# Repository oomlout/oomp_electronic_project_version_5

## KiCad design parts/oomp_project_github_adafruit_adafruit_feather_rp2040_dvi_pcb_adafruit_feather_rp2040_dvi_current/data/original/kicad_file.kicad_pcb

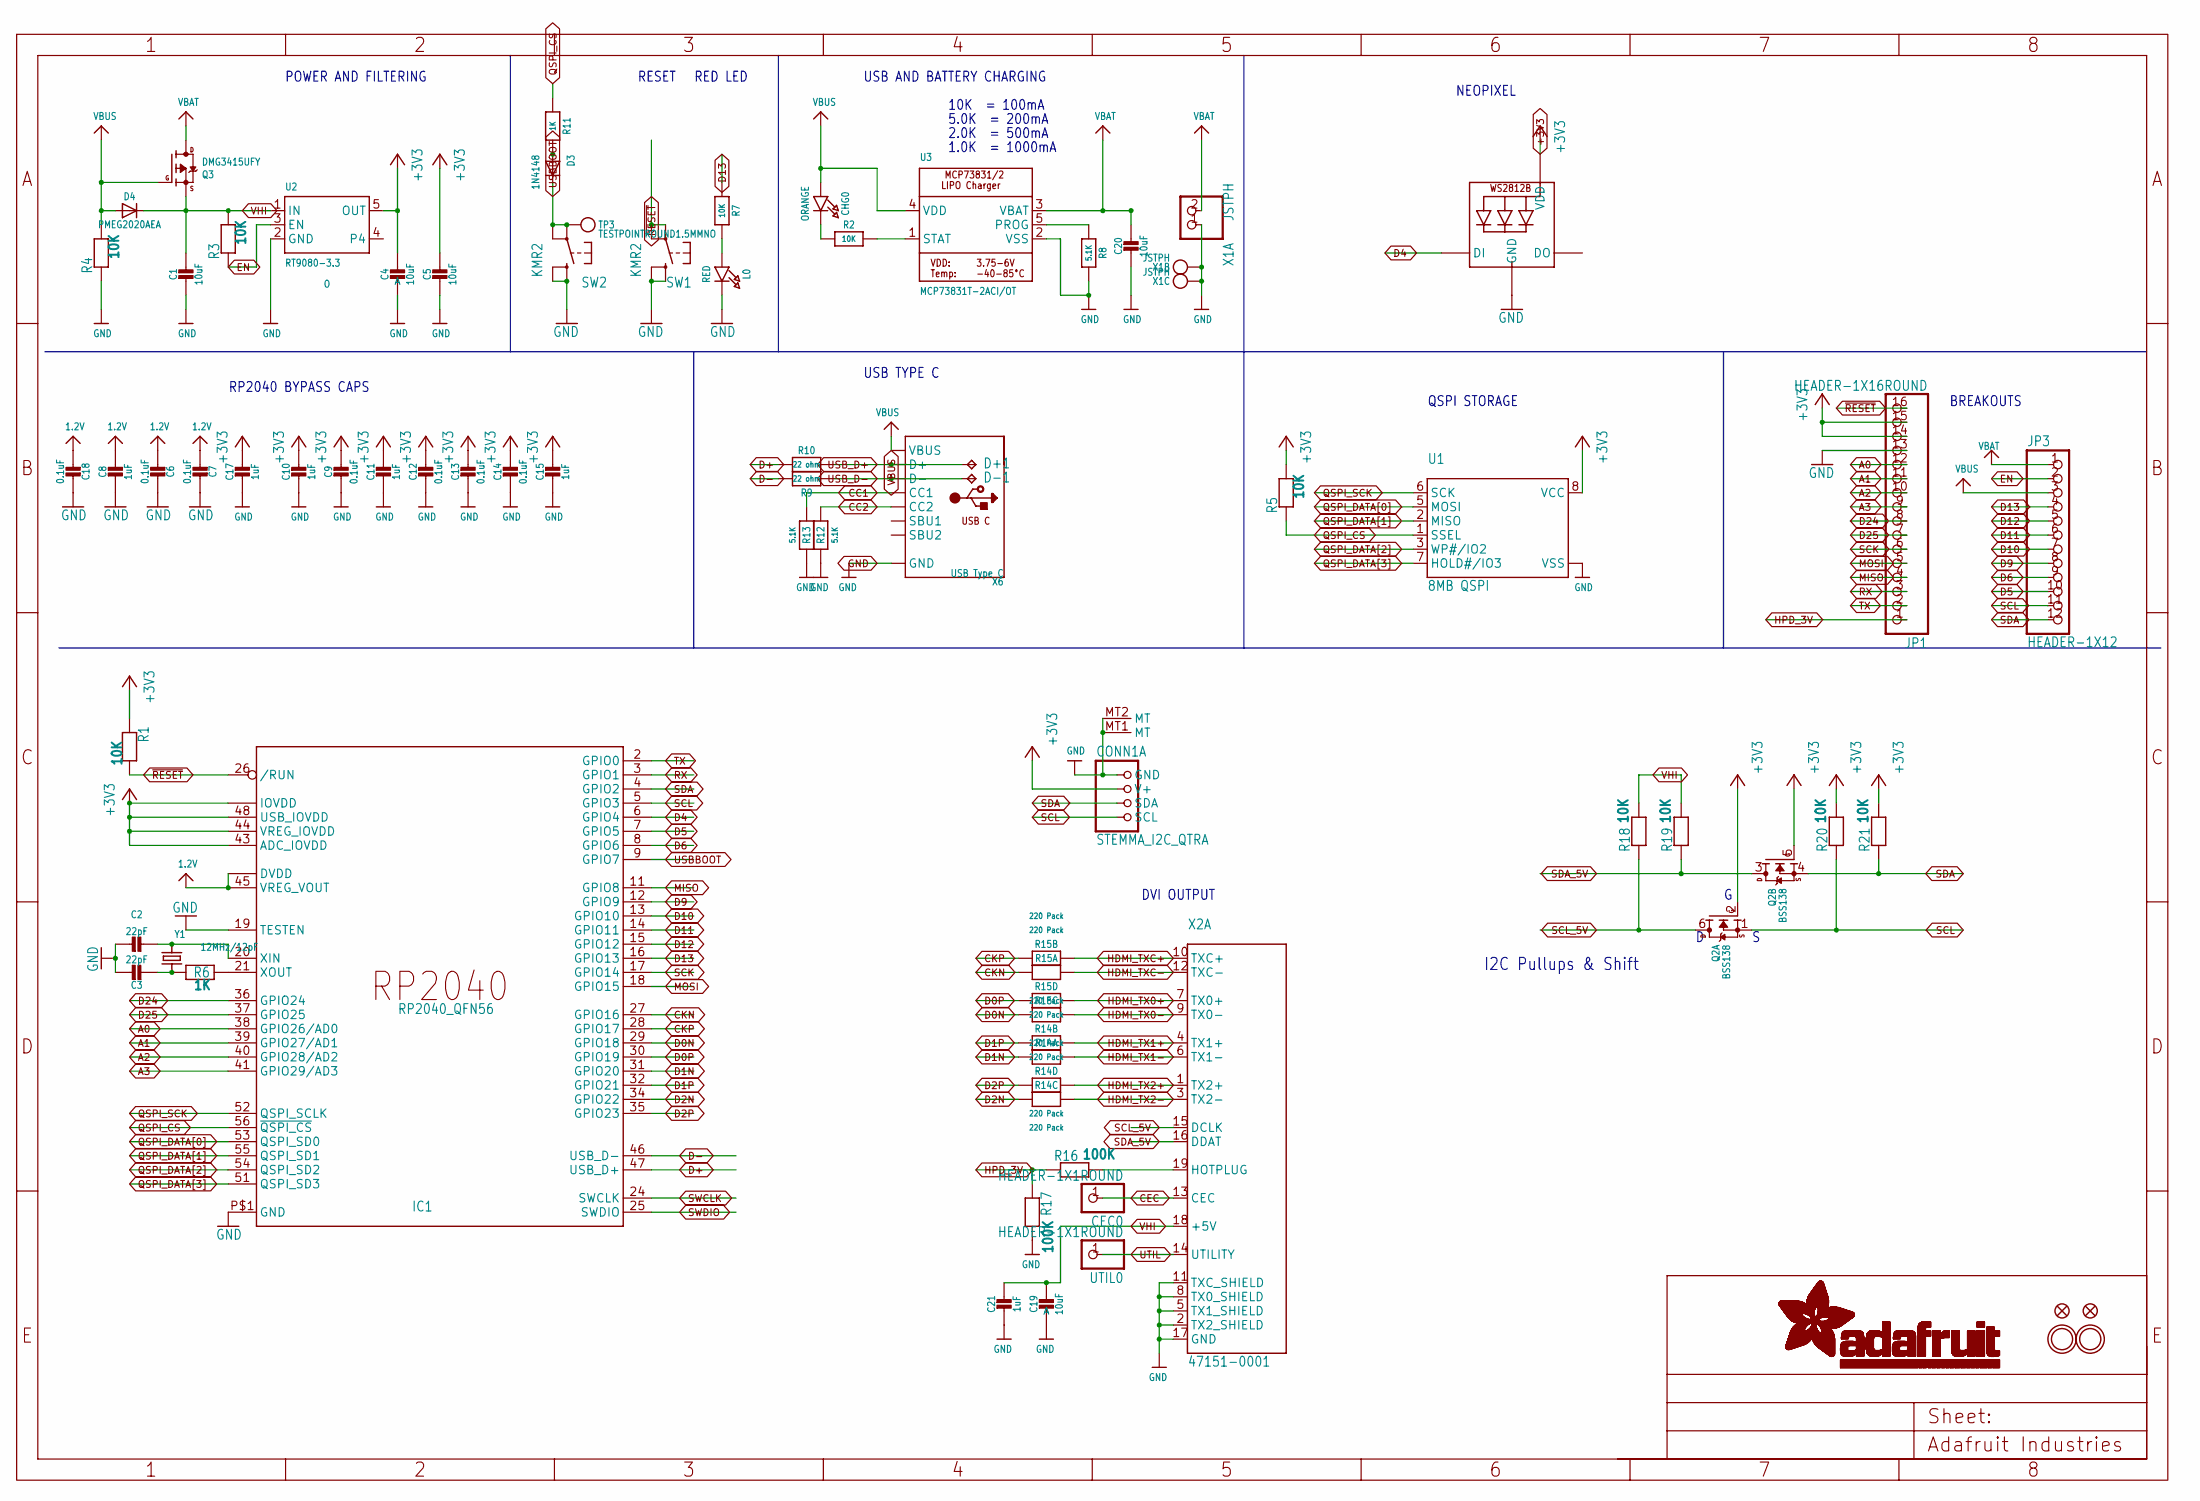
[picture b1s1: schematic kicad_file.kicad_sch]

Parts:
C1, C4, C5, C19, C20: 10uF; 0805-NO
C2, C3: 22pF; _0402NO
C6, C7, C9, C12, C13, C14, C18: 0.1uF; _0402NO
C8, C10, C11, C15, C17, C21: 1uF; _0402NO
CEC0: HEADER-1X1ROUND; 1X01_ROUND
CHG0: ORANGE; CHIPLED_0603_NOOUTLINE
CONN1: STEMMA_I2C_QTRA; JST_SH4_RA; LCSC C145961
D3: 1N4148; SOD-323F
D4: PMEG2020AEA; SOD-323F
D+1: TPB1,27; B1,27
D-1: TPB1,27; B1,27
IC1: RP2040_QFN56; QFN56_7MM_REDUCEDEPAD; LCSC C2040
JP1: HEADER-1X16ROUND; 1X16_ROUND
JP3: HEADER-1X12; 1X12_ROUND
L0: RED; CHIPLED_0603_NOOUTLINE
LED1: WS2812B_SK6805_1515; SK6805_1515; LCSC C2890035
Q2: BSS138; SOT363; JLC_ROTATION 270
Q3: DMG3415UFY; DFN2015-3
R1, R2, R3, R4, R5, R7, R18, R19, R20, R21: 10K; _0402NO
R6, R11: 1K; _0402NO
R8, R12, R13: 5.1K; _0402NO
R9, R10: 22 ohm; _0402NO
R14, R15: 220 Pack; RESPACK_4X0603
R16, R17: 100K; _0402NO
SW1, SW2: KMR2; BTN_RKB2_4.6X2.8
TP3: TESTPOINTROUND1.5MMNO; TESTPOINT_ROUND_1.5MM_NO
U1: 8MB QSPI; USON8_4X4
U2: RT9080-3.3; SOT23-5; JLC_ROTATION 0
U3: MCP73831T-2ACI/OT; SOT23-5; JLC_ROTATION 270
U$31, U$32: MOUNTINGHOLE2.5; MOUNTINGHOLE_2.5_PLATED
U$34, U$35: FIDUCIAL_1MM
UTIL0: HEADER-1X1ROUND; 1X01_ROUND
X1: JSTPH; JSTPH2_BATT; LCSC C47647
X2: 47151-0001; HDMI_MOLEX_47151-0001; LCSC C138388
X6: USB Type C; USB_C_CUSB31-CFM2AX-01-X; LCSC C165948
Y1: 12MHz/12pF; CRYSTAL_2.5X2

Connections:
1.2V: C6.2, C7.2, C8.1, C18.2, IC1.23 (DVDD), IC1.45 (VREG_VOUT), IC1.50 (DVDD)
+3V3: C4.1, C5.1, C9.1, C10.1, C11.1, C12.1, C13.1, C14.1, C15.1, C17.1, CONN1.2 (V+), IC1.1 (IOVDD), IC1.10 (IOVDD), IC1.22 (IOVDD), IC1.33 (IOVDD), IC1.42 (IOVDD), IC1.43 (ADC_IOVDD), IC1.44 (VREG_IOVDD), IC1.48 (USB_IOVDD), IC1.49 (IOVDD), JP1.14, JP1.15, LED1.2 (VDD), Q2.2 (G), Q2.5 (G), R1.1, R5.2, R20.2, R21.2, U1.8 (VCC), U2.5 (OUT)
A0: IC1.38 (GPIO26/AD0), JP1.12
A1: IC1.39 (GPIO27/AD1), JP1.11
A2: IC1.40 (GPIO28/AD2), JP1.10
A3: IC1.41 (GPIO29/AD3), JP1.9
CC1: R13.2, X6.A5 (CC1)
CC2: R12.2, X6.B5 (CC2)
CEC: CEC0.1, X2.13 (CEC)
CKN: IC1.27 (GPIO16), R15.8 (2)
CKP: IC1.28 (GPIO17), R15.7 (2)
D0N: IC1.29 (GPIO18), R15.6 (2)
D0P: IC1.30 (GPIO19), R15.5 (2)
D1N: IC1.31 (GPIO20), R14.8 (2)
D1P: IC1.32 (GPIO21), R14.7 (2)
D2N: IC1.34 (GPIO22), R14.6 (2)
D2P: IC1.35 (GPIO23), R14.5 (2)
D4: IC1.6 (GPIO4), LED1.1 (DI)
D5: IC1.7 (GPIO5), JP3.10
D6: IC1.8 (GPIO6), JP3.9
D9: IC1.12 (GPIO9), JP3.8
D10: IC1.13 (GPIO10), JP3.7
D11: IC1.14 (GPIO11), JP3.6
D12: IC1.15 (GPIO12), JP3.5
D13: IC1.16 (GPIO13), JP3.4, R7.1
D24: IC1.36 (GPIO24), JP1.8
D25: IC1.37 (GPIO25), JP1.7
D+: IC1.47 (USB_D+), R10.2
D-: IC1.46 (USB_D-), R9.2
EN: JP3.2, R3.1, U2.3 (EN)
GND: C1.2, C2.1, C3.1, C4.2, C5.2, C6.1, C7.1, C8.2, C9.2, C10.2, C11.2, C12.2, C13.2, C14.2, C15.2, C17.2, C18.1, C19.2, C20.2, C21.2, CONN1.1 (GND), CONN1.MT1 (MT), CONN1.MT2 (MT), IC1.19 (TESTEN), IC1.P$1 (GND), JP1.13, L0.C, LED1.4 (GND), R4.1, R8.2, R12.1, R13.1, R17.2, SW1.B (S), SW1.B' (S1), SW2.B (S), SW2.B' (S1), U1.4 (VSS), U1.PAD (VSS), U2.2 (GND), U3.2 (VSS), X1.1, X1.NC1, X1.NC2, X2.2 (TX2_SHIELD), X2.5 (TX1_SHIELD), X2.8 (TX0_SHIELD), X2.11 (TXC_SHIELD), X2.17 (GND), X2.P$1 (GND), X2.P$2 (GND), X2.P$3 (GND), X2.P$4 (GND), X6.A1B12 (GND), X6.B1A12 (GND)
HDMI_TX0+: R15.4 (1), X2.7 (TX0+)
HDMI_TX0-: R15.3 (1), X2.9 (TX0-)
HDMI_TX1+: R14.2 (1), X2.4 (TX1+)
HDMI_TX1-: R14.1, X2.6 (TX1-)
HDMI_TX2+: R14.4 (1), X2.1 (TX2+)
HDMI_TX2-: R14.3 (1), X2.3 (TX2-)
HDMI_TXC+: R15.2 (1), X2.10 (TXC+)
HDMI_TXC-: R15.1, X2.12 (TXC-)
HPD: R16.2, X2.19 (HOTPLUG)
HPD_3V: JP1.1, R16.1, R17.1
MISO: IC1.11 (GPIO8), JP1.4
MOSI: IC1.18 (GPIO15), JP1.5
unnamed: CHG0.C, R2.1
unnamed: L0.A, R7.2
unnamed: R2.2, U3.1 (STAT)
unnamed: R8.1, U3.5 (PROG)
unnamed: C2.2, IC1.20 (XIN), Y1.3 (2)
unnamed: C3.2, R6.1, Y1.1
unnamed: IC1.21 (XOUT), R6.2
unnamed: D3.A, R11.2
QSPI_CS: IC1.56 (~QSPI_CS), R5.1, R11.1, U1.1 (SSEL)
QSPI_DATA[0]: IC1.53 (QSPI_SD0), U1.5 (MOSI)
QSPI_DATA[1]: IC1.55 (QSPI_SD1), U1.2 (MISO)
QSPI_DATA[2]: IC1.54 (QSPI_SD2), U1.3 (WP#/IO2)
QSPI_DATA[3]: IC1.51 (QSPI_SD3), U1.7 (HOLD#/IO3)
QSPI_SCK: IC1.52 (QSPI_SCLK), U1.6 (SCK)
RX: IC1.3 (GPIO1), JP1.3
SCK: IC1.17 (GPIO14), JP1.6
SCL: CONN1.4 (SCL), IC1.5 (GPIO3), JP3.11, Q2.1 (S), R20.1
SCL_5V: Q2.6 (D), R18.1, X2.15 (DCLK)
SDA: CONN1.3 (SDA), IC1.4 (GPIO2), JP3.12, Q2.4 (S), R21.1
SDA_5V: Q2.3 (D), R19.1, X2.16 (DDAT)
SWCLK: IC1.24 (SWCLK)
SWDIO: IC1.25 (SWDIO)
TX: IC1.2 (GPIO0), JP1.2
USBBOOT: D3.C, IC1.9 (GPIO7), SW2.A, SW2.A' (P1), TP3.P$1
USB_D+: D+1.TP, R10.1, X6.A6 (D+), X6.B6 (D+)
USB_D-: D-1.TP, R9.1, X6.A7 (D-), X6.B7 (D-)
UTIL: UTIL0.1, X2.14 (UTILITY)
VBAT: C20.1, JP3.1, Q3.3 (D), U3.3 (VBAT), X1.2
VBUS: CHG0.A, D4.A, JP3.3, Q3.1 (G), R4.2, U3.4 (VDD), X6.A4B9 (VBUS), X6.B4A9 (VBUS)
VHI: C1.1, C19.1, C21.1, D4.C, Q3.2 (S), R3.2, R18.2, R19.2, U2.1 (IN), X2.18 (+5V)
~RESET: IC1.26 (/RUN), JP1.16, R1.2, SW1.A, SW1.A' (P1)

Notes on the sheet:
5.0K = 200mA
1.0K = 1000mA
NEOPIXEL
DVI OUTPUT
BREAKOUTS
USB AND BATTERY CHARGING
RP2040 BYPASS CAPS
USB TYPE C
RESET
10K = 100mA
POWER AND FILTERING
2.0K = 500mA
RED LED
I2C Pullups & Shift
QSPI STORAGE

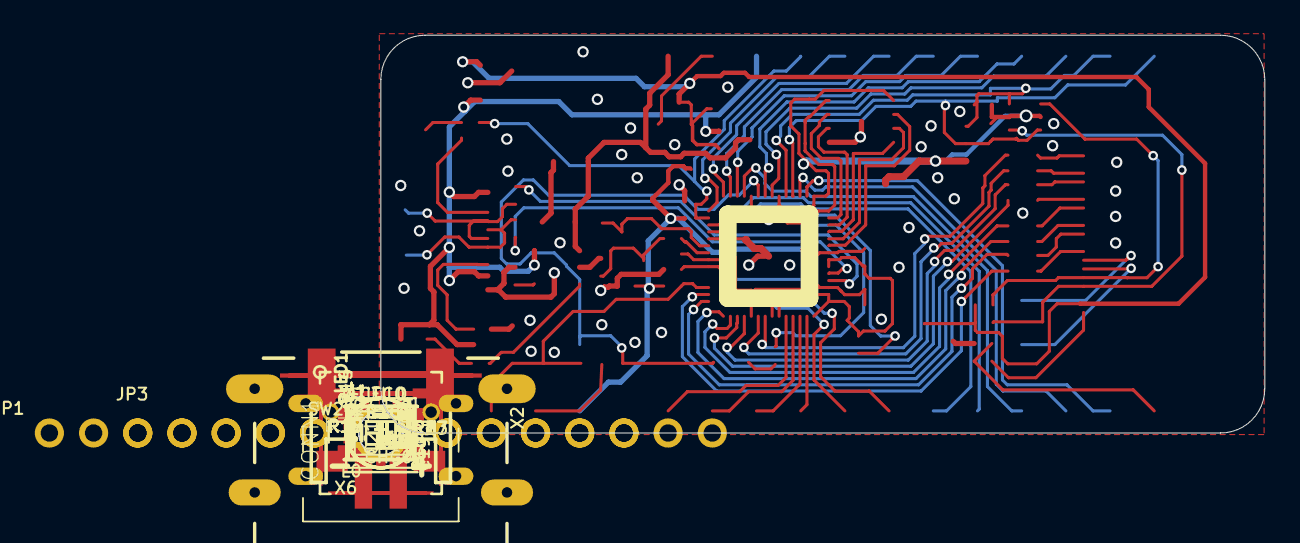
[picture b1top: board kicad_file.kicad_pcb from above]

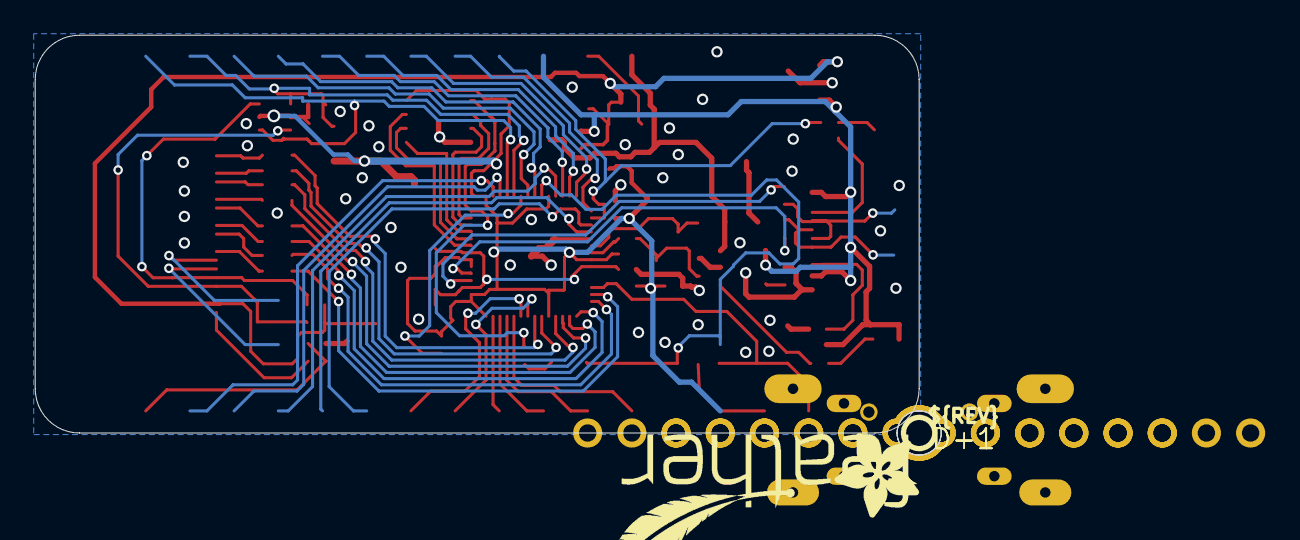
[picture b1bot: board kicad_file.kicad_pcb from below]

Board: 2 copper layers, 50.8 x 22.9 mm, 143 parts (38 on the bottom side), 72 nets.

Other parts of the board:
PLABEL0: PLABEL0
PLABEL1: PLABEL1
PLABEL2: PLABEL2
PLABEL3: PLABEL3
PLABEL4: PLABEL4
PLABEL5: PLABEL5
PLABEL6: PLABEL6
PLABEL7: PLABEL7
PLABEL8: PLABEL8
PLABEL9: PLABEL9
PLABEL10: PLABEL10
PLABEL11: PLABEL11
PLABEL12: PLABEL12
PLABEL13: PLABEL13
PLABEL14: PLABEL14
PLABEL15: PLABEL15
PLABEL16: PLABEL16
PLABEL17: PLABEL17
PLABEL18: PLABEL18
PLABEL19: PLABEL19
PLABEL20: PLABEL20
PLABEL21: PLABEL21
PLABEL22: PLABEL22
PLABEL23: PLABEL23
PLABEL24: PLABEL24
PLABEL25: PLABEL25
PLABEL26: PLABEL26
PLABEL27: PLABEL27
PLABEL28: PLABEL28
PLABEL29: PLABEL29
PLABEL30: PLABEL30
PLABEL31: PLABEL31
PLABEL32: PLABEL32
PLABEL33: PLABEL33
PLABEL34: PLABEL34
PLABEL35: PLABEL35
PLABEL36: PLABEL36
PLABEL37: PLABEL37
PLABEL38: PLABEL38
PLABEL39: PLABEL39
PLABEL40: PLABEL40
PLABEL41: PLABEL41
PLABEL42: PLABEL42
PLABEL43: PLABEL43
PLABEL44: PLABEL44
PLABEL45: PLABEL45
PLABEL46: PLABEL46
PLABEL47: PLABEL47
PLABEL48: PLABEL48
PLABEL49: PLABEL49
PLABEL50: PLABEL50
PLABEL51: PLABEL51
PLABEL52: PLABEL52
PLABEL53: PLABEL53
PLABEL54: PLABEL54
PLABEL55: PLABEL55
PLABEL56: PLABEL56
PLABEL57: PLABEL57
PLABEL58: PLABEL58
PLABEL59: PLABEL59
PLABEL60: PLABEL60
PLABEL61: PLABEL61
PLABEL62: PLABEL62
PLABEL63: PLABEL63
PLABEL64: PLABEL64
PLABEL65: PLABEL65
PLABEL66: PLABEL66
PLABEL67: PLABEL67
U$13: PCBFEAT-REV-040
U$42: FEATHERLOGO_MED
U$46: ADAFRUIT_5MM
UNK_HOLE_0: dummyfp0
UNK_HOLE_1: dummyfp1

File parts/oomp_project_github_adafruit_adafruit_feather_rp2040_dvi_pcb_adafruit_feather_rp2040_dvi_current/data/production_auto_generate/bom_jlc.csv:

Comment,Designator,Footprint,LCSC Part #
,CEC0,Adafruit Feather RP2040 DVI-import-fps:1X01_ROUND,
,UTIL0,Adafruit Feather RP2040 DVI-import-fps:1X01_ROUND,C7501259
,JP3,Adafruit Feather RP2040 DVI-import-fps:1X12_ROUND,C7501588
,JP1,Adafruit Feather RP2040 DVI-import-fps:1X16_ROUND,C7501270
,U$46,Adafruit Feather RP2040 DVI-import-fps:ADAFRUIT_5MM,
,U$42,Adafruit Feather RP2040 DVI-import-fps:FEATHERLOGO_MED,
,U$13,Adafruit Feather RP2040 DVI-import-fps:PCBFEAT-REV-040,
,PLABEL0,Adafruit Feather RP2040 DVI-import-fps:PLABEL0,
,PLABEL1,Adafruit Feather RP2040 DVI-import-fps:PLABEL1,
,PLABEL10,Adafruit Feather RP2040 DVI-import-fps:PLABEL10,
,PLABEL11,Adafruit Feather RP2040 DVI-import-fps:PLABEL11,
,PLABEL12,Adafruit Feather RP2040 DVI-import-fps:PLABEL12,
,PLABEL13,Adafruit Feather RP2040 DVI-import-fps:PLABEL13,
,PLABEL14,Adafruit Feather RP2040 DVI-import-fps:PLABEL14,
,PLABEL15,Adafruit Feather RP2040 DVI-import-fps:PLABEL15,
,PLABEL16,Adafruit Feather RP2040 DVI-import-fps:PLABEL16,
,PLABEL17,Adafruit Feather RP2040 DVI-import-fps:PLABEL17,
,PLABEL18,Adafruit Feather RP2040 DVI-import-fps:PLABEL18,
,PLABEL19,Adafruit Feather RP2040 DVI-import-fps:PLABEL19,
,PLABEL2,Adafruit Feather RP2040 DVI-import-fps:PLABEL2,
,PLABEL20,Adafruit Feather RP2040 DVI-import-fps:PLABEL20,
,PLABEL21,Adafruit Feather RP2040 DVI-import-fps:PLABEL21,
,PLABEL22,Adafruit Feather RP2040 DVI-import-fps:PLABEL22,
,PLABEL23,Adafruit Feather RP2040 DVI-import-fps:PLABEL23,
,PLABEL24,Adafruit Feather RP2040 DVI-import-fps:PLABEL24,
,PLABEL25,Adafruit Feather RP2040 DVI-import-fps:PLABEL25,
,PLABEL26,Adafruit Feather RP2040 DVI-import-fps:PLABEL26,
,PLABEL27,Adafruit Feather RP2040 DVI-import-fps:PLABEL27,
,PLABEL28,Adafruit Feather RP2040 DVI-import-fps:PLABEL28,
,PLABEL29,Adafruit Feather RP2040 DVI-import-fps:PLABEL29,
,PLABEL3,Adafruit Feather RP2040 DVI-import-fps:PLABEL3,
,PLABEL30,Adafruit Feather RP2040 DVI-import-fps:PLABEL30,
,PLABEL31,Adafruit Feather RP2040 DVI-import-fps:PLABEL31,
,PLABEL32,Adafruit Feather RP2040 DVI-import-fps:PLABEL32,
,PLABEL33,Adafruit Feather RP2040 DVI-import-fps:PLABEL33,
,PLABEL34,Adafruit Feather RP2040 DVI-import-fps:PLABEL34,
,PLABEL35,Adafruit Feather RP2040 DVI-import-fps:PLABEL35,
,PLABEL36,Adafruit Feather RP2040 DVI-import-fps:PLABEL36,
,PLABEL37,Adafruit Feather RP2040 DVI-import-fps:PLABEL37,
,PLABEL38,Adafruit Feather RP2040 DVI-import-fps:PLABEL38,
,PLABEL39,Adafruit Feather RP2040 DVI-import-fps:PLABEL39,
,PLABEL4,Adafruit Feather RP2040 DVI-import-fps:PLABEL4,
,PLABEL40,Adafruit Feather RP2040 DVI-import-fps:PLABEL40,
,PLABEL41,Adafruit Feather RP2040 DVI-import-fps:PLABEL41,
,PLABEL42,Adafruit Feather RP2040 DVI-import-fps:PLABEL42,
,PLABEL43,Adafruit Feather RP2040 DVI-import-fps:PLABEL43,
,PLABEL44,Adafruit Feather RP2040 DVI-import-fps:PLABEL44,
,PLABEL45,Adafruit Feather RP2040 DVI-import-fps:PLABEL45,
,PLABEL46,Adafruit Feather RP2040 DVI-import-fps:PLABEL46,
,PLABEL47,Adafruit Feather RP2040 DVI-import-fps:PLABEL47,
,PLABEL48,Adafruit Feather RP2040 DVI-import-fps:PLABEL48,
,PLABEL49,Adafruit Feather RP2040 DVI-import-fps:PLABEL49,
,PLABEL5,Adafruit Feather RP2040 DVI-import-fps:PLABEL5,
,PLABEL50,Adafruit Feather RP2040 DVI-import-fps:PLABEL50,
,PLABEL51,Adafruit Feather RP2040 DVI-import-fps:PLABEL51,
,PLABEL52,Adafruit Feather RP2040 DVI-import-fps:PLABEL52,
,PLABEL53,Adafruit Feather RP2040 DVI-import-fps:PLABEL53,
,PLABEL54,Adafruit Feather RP2040 DVI-import-fps:PLABEL54,
,PLABEL55,Adafruit Feather RP2040 DVI-import-fps:PLABEL55,
,PLABEL56,Adafruit Feather RP2040 DVI-import-fps:PLABEL56,
,PLABEL57,Adafruit Feather RP2040 DVI-import-fps:PLABEL57,
,PLABEL58,Adafruit Feather RP2040 DVI-import-fps:PLABEL58,
,PLABEL59,Adafruit Feather RP2040 DVI-import-fps:PLABEL59,
,PLABEL6,Adafruit Feather RP2040 DVI-import-fps:PLABEL6,
,PLABEL60,Adafruit Feather RP2040 DVI-import-fps:PLABEL60,
,PLABEL61,Adafruit Feather RP2040 DVI-import-fps:PLABEL61,
,PLABEL62,Adafruit Feather RP2040 DVI-import-fps:PLABEL62,
,PLABEL63,Adafruit Feather RP2040 DVI-import-fps:PLABEL63,
,PLABEL64,Adafruit Feather RP2040 DVI-import-fps:PLABEL64,
,PLABEL65,Adafruit Feather RP2040 DVI-import-fps:PLABEL65,
,PLABEL66,Adafruit Feather RP2040 DVI-import-fps:PLABEL66,
,PLABEL67,Adafruit Feather RP2040 DVI-import-fps:PLABEL67,
,PLABEL7,Adafruit Feather RP2040 DVI-import-fps:PLABEL7,
,PLABEL8,Adafruit Feather RP2040 DVI-import-fps:PLABEL8,
,PLABEL9,Adafruit Feather RP2040 DVI-import-fps:PLABEL9,
,TP3,Adafruit Feather RP2040 DVI-import-fps:TESTPOINT_ROUND_1.5MM_NO,
0.1uF,"C6,C7,C9,C12,C13,C14,C18",Adafruit Feather RP2040 DVI-import-fps:_0402NO,C60474
100K,"R16,R17",Adafruit Feather RP2040 DVI-import-fps:_0402NO,C25530
10K,"R1,R2,R3,R4,R5,R7,R18,R19,R20,R21",Adafruit Feather RP2040 DVI-import-fps:_0402NO,C2906861
10uF,"C1,C4,C5,C19,C20",Adafruit Feather RP2040 DVI-import-fps:0805-NO,
12MHz/12pF,Y1,Adafruit Feather RP2040 DVI-import-fps:CRYSTAL_2.5X2,
1K,"R6,R11",Adafruit Feather RP2040 DVI-import-fps:_0402NO,C2906864
1N4148,D3,Adafruit Feather RP2040 DVI-import-fps:SOD-323F,
1uF,"C8,C10,C11,C15,C17,C21",Adafruit Feather RP2040 DVI-import-fps:_0402NO,C2887021
22 ohm,"R9,R10",Adafruit Feather RP2040 DVI-import-fps:_0402NO,C114765
220 Pack,"R14,R15",Adafruit Feather RP2040 DVI-import-fps:RESPACK_4X0603,
22pF,"C2,C3",Adafruit Feather RP2040 DVI-import-fps:_0402NO,C106203
47151-0001,X2,Adafruit Feather RP2040 DVI-import-fps:HDMI_MOLEX_47151-0001,
5.1K,"R8,R12,R13",Adafruit Feather RP2040 DVI-import-fps:_0402NO,C25905
8MB QSPI,U1,Adafruit Feather RP2040 DVI-import-fps:USON8_4X4,
BSS138,Q2,Adafruit Feather RP2040 DVI-import-fps:SOT363,
DMG3415UFY,Q3,Adafruit Feather RP2040 DVI-import-fps:DFN2015-3,
FIDUCIAL_1MM,"U$34,U$35",Adafruit Feather RP2040 DVI-import-fps:FIDUCIAL_1MM,
JSTPH,X1,Adafruit Feather RP2040 DVI-import-fps:JSTPH2_BATT,
KMR2,"SW1,SW2",Adafruit Feather RP2040 DVI-import-fps:BTN_RKB2_4.6X2.8,
MCP73831T-2ACI/OT,U3,Adafruit Feather RP2040 DVI-import-fps:SOT23-5,
ORANGE,CHG0,Adafruit Feather RP2040 DVI-import-fps:CHIPLED_0603_NOOUTLINE,
PMEG2020AEA,D4,Adafruit Feather RP2040 DVI-import-fps:SOD-323F,
RED,L0,Adafruit Feather RP2040 DVI-import-fps:CHIPLED_0603_NOOUTLINE,
RP2040_QFN56,IC1,Adafruit Feather RP2040 DVI-import-fps:QFN56_7MM_REDUCEDEPAD,
RT9080-3.3,U2,Adafruit Feather RP2040 DVI-import-fps:SOT23-5,
STEMMA_I2C_QTRA,CONN1,Adafruit Feather RP2040 DVI-import-fps:JST_SH4_RA,
"TPB1,27","D+1,D-1","Adafruit Feather RP2040 DVI-import-fps:B1,27",
USB Type C,X6,Adafruit Feather RP2040 DVI-import-fps:USB_C_CUSB31-CFM2AX-01-X,
WS2812B_SK6805_1515,LED1,Adafruit Feather RP2040 DVI-import-fps:SK6805_1515,
